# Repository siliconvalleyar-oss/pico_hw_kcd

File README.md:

# XiaoZhi - Asistente de Voz con  Raspberry pico (Versión Multisensor)

Repositorio del diseño PCB para el dispositivo **XiaoZhi**, una estación de desarrollo y asistente de voz de código abierto basado en el ****. Este diseño integra audio digital de alta calidad, iluminación RGB, pantalla OLED, **pantalla TFT**, **sensores ambientales (gas, temperatura/humedad, distancia)** y **comunicación CAN** en una sola placa diseñada con **KiCad**.

---

## 📖 Descripción

XiaoZhi evoluciona para convertirse en un nodo IoT multisensor ideal para automatización del hogar, monitoreo industrial o robótica. Además de la interacción por voz (micrófono y altavoz), la placa incorpora:

- **MQ-6**: Detección de gases combustibles (LPG, butano, metano).
- **AHT21B**: Medición precisa de temperatura y humedad ambiental (I2C).
- **VL53L0X**: Sensor de distancia por tiempo de vuelo (ToF) de hasta 2 metros.
- **ST7789**: Pantalla TFT a color para gráficos avanzados (SPI).
- **MCP2515**: Controlador CAN bus (con transceptor) para comunicación vehicular o industrial.

Todo ello manteniendo la conectividad Wi-Fi 6, BLE 5.0 y la interfaz USB-UART integrada.

---

## ✨ Características Principales

- **Microcontrolador**: Raspberry pico (RISC-V dual-core, Wi-Fi 6, BLE 5.0, Zigbee/Thread).
- **Audio**:
  - Micrófono MEMS **INMP441** (I2S).
  - Amplificador **MAX98357A** (I2S) para altavoz externo.
- **Interfaz y depuración**: **FT232** integrado para USB-UART.
- **Iluminación y control**:
  - LED GPIO estándar y LED direccionable **WS2812**.
  - Pulsadores (BOOT y RESET).
- **Pantallas**:
  - **SSD1306** (OLED 128x64, I2C) para información rápida.
  - **ST7789** (TFT a color, SPI) para gráficos, menús o visualización de datos.
- **Sensores**:
  - **MQ-6** (gas) – Salida analógica (ADC).
  - **AHT21B** (temperatura/humedad) – I2C.
  - **VL53L0X** (distancia ToF) – I2C.
- **Comunicación industrial**:
  - **MCP2515** + transceptor CAN (SPI) para bus CAN 2.0.
- **Alimentación**: 5V vía USB-C, con reguladores internos para 3.3V.

---

## 📦 Lista de Componentes (BOM)

| Componente | Cantidad | Descripción | Referencia en PCB |
| :--- | :--- | :--- | :--- |
| Raspberry pico| 1 | Módulo Wi-Fi/BLE/Zigbee | U1 |
| INMP441 | 1 | Micrófono MEMS I2S | U2 |
| MAX98357A | 1 | Amplificador Clase D I2S | U3 |
| FT232RL (o FT232RQ) | 1 | Conversor USB-UART | U4 |
| WS2812B | 1 (o N) | LED RGB direccionable | D1 |
| LED (GPIO) | 1 | LED indicador estándar | D2 |
| SWITCH (Push Button) | 2 | Pulsadores (BOOT y RESET) | SW1, SW2 |
| SSD1306 (I2C) | 1 | Display OLED de 0.96" | OLED1 |
| **MQ-6** | **1** | **Sensor de gas (LPG, butano, metano)** | **U6** |
| **AHT21B** | **1** | **Sensor de temperatura y humedad (I2C)** | **U7** |
| **VL53L0X** | **1** | **Sensor de distancia ToF (Time-of-Flight)** | **U8** |
| **ST7789** | **1** | **Pantalla TFT a color (SPI) - 1.3" / 1.54"** | **U9** |
| **PN532**|**1**|NFC |
| **MCP2515** | **1** | **Controlador CAN (SPI) + TJA1050 (transceptor)** | **U10** |
| Regulador 3.3V (AMS1117) | 1 | LDO para alimentación interna | U5 |
| Cristal 6MHz | 1 | Oscilador para FT232 (según esquema) | X1 |
| Resistencias, Capacitores, Conectores | Varios | Pasivos y terminales (USB-C, JST) | - |

---

## 🔌 Asignación de Pines (Pinout)

> **⚠️ Importante**: La siguiente tabla es una referencia estándar. Verifica siempre el esquemático (`*.sch`) para confirmar las conexiones finales.

| Periférico | Pin del ESP32-C6 | Descripción / Notas |
| :--- | :--- | :--- |
| **INMP441 (Mic)** | GPIO3 (I2S_BCK) | Bit Clock |
| | GPIO2 (I2S_WS) | Word Select (LRCLK) |
| | GPIO1 (I2S_DIN) | Data Output (DOUT) |
| | 3.3V / GND | Alimentación |
| **MAX98357A (Amp)** | GPIO3 (I2S_BCK) | Bit Clock (compartido) |
| | GPIO2 (I2S_WS) | Word Select (compartido) |
| | GPIO4 (I2S_DOUT) | Data Input (DIN) |
| | GPIO5 | Shutdown (SD) - Activo bajo |
| | 5V / GND | Alimentación |
| **WS2812** | GPIO6 | Data Input |
| | 5V / GND | Alimentación |
| **SSD1306 (OLED) / AHT21B / VL53L0X** | GPIO7 (I2C_SCL) | Bus I2C compartido (SCL) |
| | GPIO8 (I2C_SDA) | Bus I2C compartido (SDA) |
| | 3.3V / GND | Alimentación (todas comparten bus) |
| **FT232 (UART)** | GPIO9 (RX) | RX del ESP (conectar a TX del FT) |
| | GPIO10 (TX) | TX del ESP (conectar a RX del FT) |
| | GPIO11 (DTR) | Auto-reset (opcional) |
| **SWITCH BOOT** | GPIO12 | Boot (GPIO0 en otros chips, verificar) |
| **SWITCH RESET** | CHIP_EN | Reset (EN) |
| **LED GPIO** | GPIO13 | Ánodo del LED (con resistencia) |
| **MQ-6 (Gas)** | **GPIO14** | **Salida analógica (ADC)** |
| **ST7789 (TFT)** | **GPIO15 (SPI_MOSI)** | **Master Out / Slave In** |
| | **GPIO16 (SPI_SCLK)** | **Clock SPI** |
| | **GPIO17 (DC)** | **Data/Command** |
| | **GPIO18 (CS)** | **Chip Select (activo bajo)** |
| | **GPIO19 (RST)** | **Reset de la pantalla** |
| **MCP2515 (CAN)** | **GPIO15 (SPI_MOSI)** | **Comparte MOSI con TFT** |
| | **GPIO16 (SPI_SCLK)** | **Comparte SCLK con TFT** |
| | **GPIO20 (CS)** | **Chip Select exclusivo para CAN** |
| | **GPIO21 (INT)** | **Interrupción del MCP2515** |
| | 5V / GND | Alimentación (transceptor CAN) |

---

## 🧩 Integración de Sensores y Bus Compartido

Para optimizar los pines del Raspberry pico , el diseño utiliza buses compartidos:

- **Bus I2C (GPIO7 y GPIO8)**: Conecta simultáneamente el **SSD1306**, el **AHT21B** y el **VL53L0X**. Cada dispositivo tiene una dirección I2C única, por lo que no hay conflicto.
- **Bus SPI (GPIO15 y GPIO16)**: Conecta el **ST7789** y el **MCP2515**. Se diferencian mediante pines **CS (Chip Select)** independientes (GPIO18 para TFT, GPIO20 para CAN).
- **ADC (GPIO14)**: Reservado exclusivamente para la salida analógica del sensor de gas **MQ-6**. Se recomienda agregar un capacitor de filtrado en la PCB para estabilizar la lectura.

---

## 🛠️ Uso del Proyecto en KiCad

### Requisitos
- KiCad **v8.0** o superior.
- Símbolos y huellas adicionales para los nuevos componentes (es posible que necesites descargar librerías externas para el MCP2515, VL53L0X o ST7789).

### Abrir y Editar
1. Clona este repositorio:
   ```bash
   git clone https://github.com/tu-usuario/xiaozhi-pcb.git
   cd xiaozhi-pcb

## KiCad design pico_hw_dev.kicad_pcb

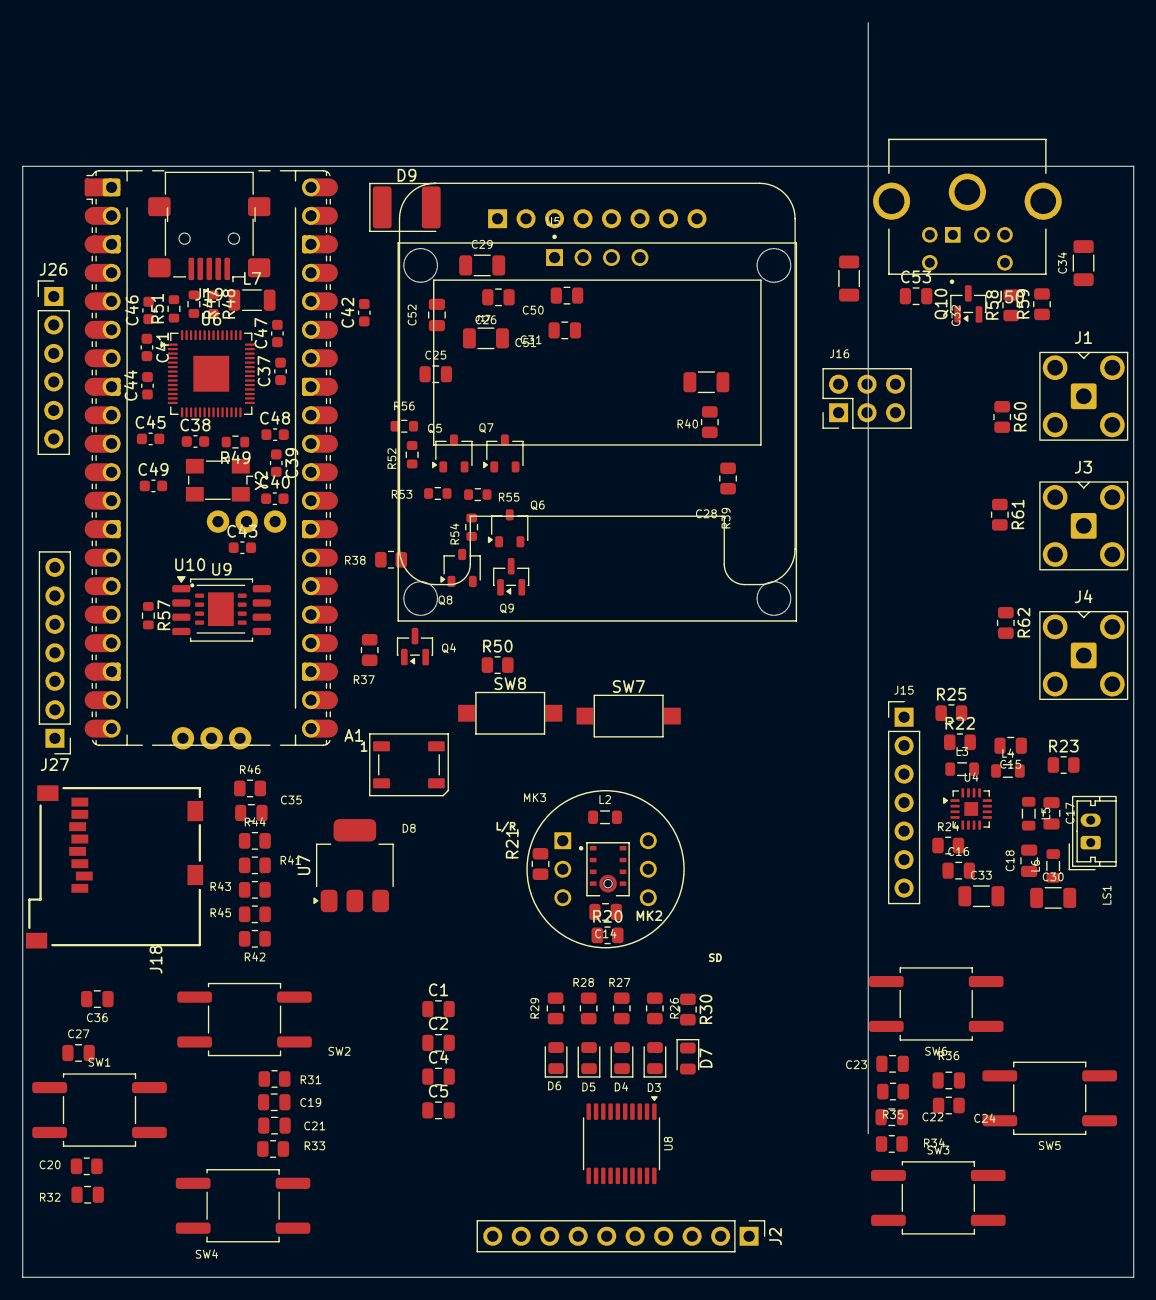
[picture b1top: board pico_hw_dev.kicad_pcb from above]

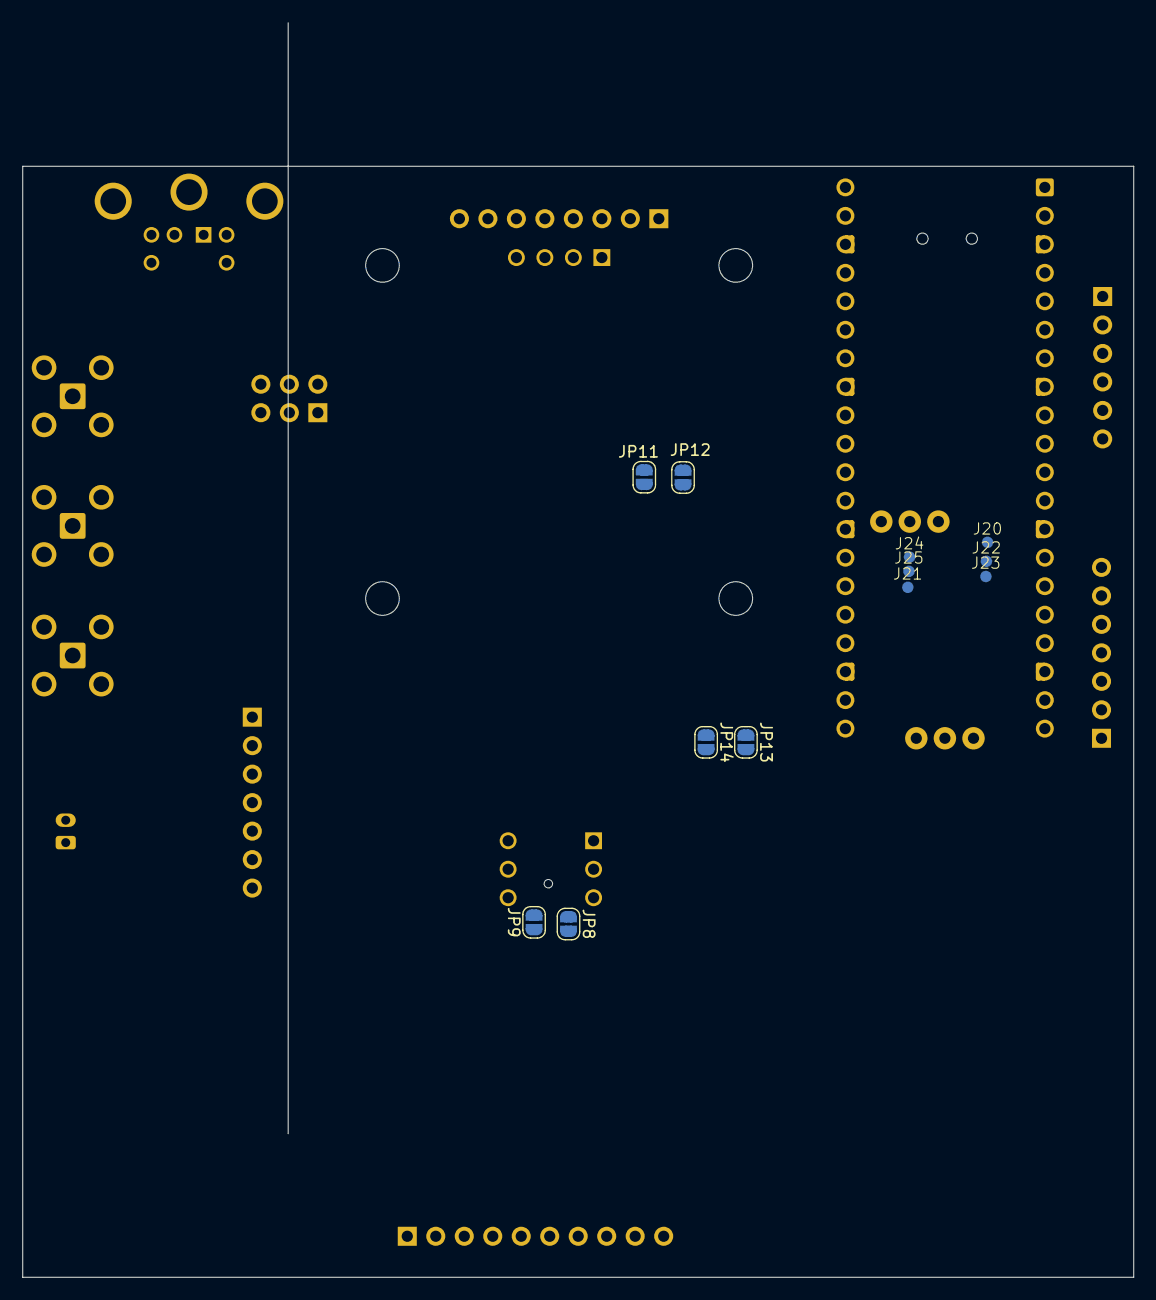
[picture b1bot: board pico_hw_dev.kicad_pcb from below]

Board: 2 copper layers, 99.1 x 99.1 mm, 151 parts (12 on the bottom side), 90 nets, no tracks yet.

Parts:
A1: RaspberryPi_Pico
C1, C2, C4, C5, C14, C15, C19, C20, C21, C22, C23, C24, C26, C27, C35, C36, C50, C51, C52: 100nf; C_0805_2012Metric
C16: 10uf; C_0805_2012Metric
C17: 220p; C_0805_2012Metric
C18: 22p; C_0805_2012Metric
C25: 100nF; C_0805_2012Metric
C28, C29, C30, C31, C32, C33, C34: 100nf; C_1206_3216Metric
C37, C38, C39, C40, C41, C42, C43, C44, C45, C46, C48: 10n; C_0603_1608Metric
C47, C49: 100nf; C_0603_1608Metric
C53: 10n; C_0805_2012Metric
D3, D4, D5, D6, D7: LED; D_0805_2012Metric
D8: WS2812B; LED_WS2812B_PLCC4_5.0x5.0mm_P3.2mm
D9: D_Schottky; D_2114_3652Metric
J1, J3, J4: Conn_Coaxial; SMA_BAT_Wireless_BWSMA-KWE-Z001
J2: LOGIC; PinHeader_1x10_P2.54mm_Vertical
J15: PinHeader_1x07_P2.54mm_Vertical
J16: Oled SSD1306 128x32; PinHeader_2x03_P2.54mm_Vertical
J17: Adafruit ST7789; Adafruit_SSD1306_No_Mounting_Holes_pads
J18: Micro_SD_Card; 3M_2908-05WB-MG
J19: USB_B_Mini; USB_Mini-B_Lumberg_2486_01_Horizontal
J20, J21, J22, J23, J24, J25: gpio_rp2040; connector_pin_smd_1mm
J26: FT232RL; PinHeader_1x06_P2.54mm_Vertical
J27: picoprobe debugger; PinHeader_1x07_P2.54mm_Vertical
J50: Mini-DIN-6; TE_5749180-1
JP8, JP9: Jumper_2_Open; SolderJumper-2_P1.3mm_Open_RoundedPad1.0x1.5mm
JP11, JP12, JP13, JP14: NL; SolderJumper-2_P1.3mm_Open_RoundedPad1.0x1.5mm
L2, L3, L4, L5, L6: ferrite; L_0805_2012Metric
L7: 100mh; L_1206_3216Metric
LS1: Speaker; Molex_Micro-Latch_53253-0270_1x02_P2.00mm_Vertical
MK2: INMP441ACEZ-R7; MIC_INMP441ACEZ-R7
MK3: INMP441ACEZ-R7; MODULE_OKY3139
Q4, Q9, Q10: 2N7002; SOT-23
Q5, Q7: Q_NPN_BCE; SOT-23W
Q6, Q8: FDN306P; SOT-23W
R20, R21, R22, R23: 100k; R_0805_2012Metric
R24: 1M; R_0805_2012Metric
R25: 68k; R_0805_2012Metric
R26, R27, R28, R29, R30, R31, R32, R33, R34, R35, R36, R37, R38, R39, R40: 2k2; R_0805_2012Metric
R41, R42, R43, R44, R45, R46: 4k7; R_0805_2012Metric
R47, R48, R49, R51, R52, R53, R54, R55, R56, R57: 10k; R_0603_1608Metric
R50, R58, R59, R60, R61, R62: 10k; R_0805_2012Metric
SW1, SW5: up; SW_Push_1P1T_NO_CK_KSC9xxG
SW2, SW6: down; SW_Push_1P1T_NO_CK_KSC9xxG
SW3: left; SW_Push_1P1T_NO_CK_KSC9xxG
SW4: rigth; SW_Push_1P1T_NO_CK_KSC9xxG
SW7: boot; SW_SPST_CK_RS282G05A3
SW8: run; SW_SPST_CK_RS282G05A3
U4: MAX98357A; TQFN-16-1EP_3x3mm_P0.5mm_EP1.23x1.23mm
U5: ER_OLEDM0.91_1x-I2C; LCD_OLED_128X64_1.3_I2C
U6: RP2040; QFN-56-1EP_7x7mm_P0.4mm_EP3.2x3.2mm
U7: R-78E3.3-0.5; SOT-223-3_TabPin2
U8: TXS0108EPW; TSSOP-20_4.4x6.5mm_P0.65mm
U9: W25Q16JVSS; SOIC-8_5.3x5.3mm_P1.27mm
U10: W25Q16JVSS; Winbond_XSON-8-1EP_4x4mm_P0.8mm_EP2.3x3.0mm
Y2: Crystal_GND24_Small; Oscillator_SMD_Fox_FT5H_5.0x3.2mm

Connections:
+1V2: C40.2, C41.2, U6.23 (DVDD), U6.45 (VREG_VOUT), U6.50 (DVDD)
+3.3V: A1.36 (3V3), A1.37 (3V3_EN), C1.1, C2.1, C4.2, C5.2, C42.2, C43.2, C44.2, C45.2, C49.2, Q10.1 (G), R50.1, R51.2, R58.2, U6.1 (IOVDD), U6.10 (IOVDD), U6.22 (IOVDD), U6.33 (IOVDD), U6.42 (IOVDD), U6.43 (ADC_AVDD), U6.44 (VREG_IN), U6.48 (USB_VDD), U6.49 (IOVDD), U7.3 (OUT), U9.8 (VCC), U10.8 (VCC)
+3V3: C26.1, C27.1, C28.1, C29.1, C30.1, C31.1, C32.1, C35.1, C36.1, C50.1, C51.1, J16.1, J17.2, J18.4 (VDD), JP8.2 (B), JP11.2 (B), L2.2, L3.2, Q4.1 (G), R24.1, R31.1, R32.1, R33.1, R34.1, R35.1, R36.1, R37.2, R39.1, R40.1, R41.1, R42.1, R43.1, R44.2, R45.1, R46.2, R53.2, R56.2, U5.2 (VCC), U8.2 (VCCA)
+5V: C25.1, C33.1, C34.1, C52.1, C53.1, D8.1 (VDD), J16.2, J16.4, J50.4, JP12.2 (B), L4.2, R38.2, R59.2, U8.19 (VCCB)
/ADC_0: A1.31 (GPIO26_ADC0), J50.1, Q10.2 (S), Q10.3 (D), R58.1, R59.1, U6.38 (GPIO26_ADC0)
/ADC_1: A1.32 (GPIO27_ADC1), J50.5, U6.39 (GPIO27_ADC1)
/ADC_2: A1.34 (GPIO28_ADC2), U6.40 (GPIO28_ADC2)
/IO_4: A1.6 (GPIO4), J15.1, U4.14 (LRCLK), U6.6 (GPIO4)
/IO_5: A1.7 (GPIO5), D5.2 (A), U6.7 (GPIO5), U8.4 (A3)
/IO_6: A1.9 (GPIO6), D6.2 (A), U6.8 (GPIO6), U8.5 (A4)
/IO_7: A1.10 (GPIO7), C20.1, R32.2, SW1.1, U6.9 (GPIO7), U8.6 (A5)
/IO_8: A1.11 (GPIO8), C19.1, R31.2, SW2.1, U6.11 (GPIO8), U8.7 (A6)
/IO_9: A1.12 (GPIO9), C22.1, R34.2, SW3.1, U6.12 (GPIO9), U8.8 (A7)
/IO_10: A1.14 (GPIO10), MK2.1 (SCK), MK3.1 (SCK), U6.13 (GPIO10)
/IO_11: A1.15 (GPIO11), MK2.3 (WS), MK3.3 (WS), U6.14 (GPIO11)
/IO_13: A1.17 (GPIO13), C21.1, R33.2, SW4.1, U6.16 (GPIO13), U8.9 (A8)
/IO_23: C24.1, R36.2, SW5.1, U6.35 (GPIO23)
/IO_24: C23.1, R35.2, SW6.1, U6.36 (GPIO24)
/IO_25: JP13.1 (A), U6.37 (GPIO25)
/Logic_convert/B1: J2.2, U8.20 (B1)
/Logic_convert/B2: J2.3, U8.18 (B2)
/Logic_convert/B3: J2.4, U8.17 (B3)
/Logic_convert/B4: J2.5, U8.16 (B4)
/Logic_convert/B5: J2.6, U8.15 (B5)
/Logic_convert/B6: J2.7, U8.14 (B6)
/Logic_convert/B7: J2.8, U8.13 (B7)
/Logic_convert/B8: J2.9, U8.12 (B8)
/Logic_convert/OEN: Q7.2 (C), R56.1, U8.10 (OE)
/Logic_convert/vcc: J2.1, Q8.2
/MISO: A1.21 (GPIO16), J18.3 (CMD), R42.2, U6.27 (GPIO16)
/WS2812: JP13.2 (B), JP14.2 (B), Q4.2 (S), Q6.1, Q9.1 (G), R37.1, R54.2
/inmp441/EN: C14.2, L2.1, MK2.7 (VDD), MK2.8 (CHIPEN)
/max98357a/OUTN: L5.1, U4.10 (OUTN)
/max98357a/OUTP: L6.1, U4.9 (OUTP)
/picohw/QSPI_CS: J20.1 (Pin_1_1), R51.1, R57.1, U6.56 (QSPI_SS), U9.1 (~CS), U10.1 (~CS)
/picohw/QSPI_SCLK: J25.1 (Pin_1_1), U6.52 (QSPI_SCLK), U9.6 (CLK), U10.6 (CLK)
/picohw/QSPI_SD0: J21.1 (Pin_1_1), U6.53 (QSPI_SD0), U9.5 (DI/IO_{0}), U10.5 (DI/IO_{0})
/picohw/QSPI_SD1: J22.1 (Pin_1_1), U6.55 (QSPI_SD1), U9.2 (DO/IO_{1}), U10.2 (DO/IO_{1})
/picohw/QSPI_SD2: J23.1 (Pin_1_1), U6.54 (QSPI_SD2), U9.3 (~WP/IO_{2}), U10.3 (~WP/IO_{2})
/picohw/QSPI_SD3: J24.1 (Pin_1_1), U6.51 (QSPI_SD3), U9.7 (~HOLD/~RESET/IO_{3}), U10.7 (~HOLD/~RESET/IO_{3})
/picohw/RUN: A1.30 (RUN), C48.1, R50.2, SW8.2, U6.26 (RUN)
/picohw/USB_DM: R47.2, U6.46 (USB_DM)
/picohw/USB_DP: R48.2, U6.47 (USB_DP)
/picohw/XIN: C38.1, U6.20 (XIN), Y2.3
/picohw/XOUT: R49.2, U6.21 (XOUT)
/swclk: J27.5, U6.24 (SWCLK)
/swdio: J27.4, U6.25 (SWD)
BLK_ST7789: A1.29 (GPIO22), J17.7, U6.34 (GPIO22)
CLK_ST7789: A1.19 (GPIO14), J17.4, U6.17 (GPIO14)
CS_RP2040: A1.22 (GPIO17), J18.2 (DAT3/CD), R43.2, U6.28 (GPIO17)
DC_ST7789: A1.27 (GPIO21), J16.5, J17.6, R39.2, U5.3 (SCL), U6.32 (GPIO21)
DI_ST7789: A1.20 (GPIO15), J17.3, U6.18 (GPIO15)
GAIN: J15.4, R22.2, R23.1, U4.2 (GAIN_SLOT)
GND: A1.3 (GND), A1.8 (GND), A1.13 (GND), A1.18 (GND), A1.23 (GND), A1.28 (GND), A1.33 (AGND), A1.38 (GND), C1.2, C2.2, C4.1, C5.1, C14.1, C15.1, C16.1, C17.1, C18.1, C19.2, C20.2, C21.2, C22.2, C23.2, C24.2, C25.2, C26.2, C27.2, C28.2, C29.2, C30.2, C31.2, C32.2, C33.2, C34.2, C35.2, C36.2, C37.1, C38.2, C39.2, C40.1, C41.1, C42.1, C43.1, C44.1, C45.1, C46.2, C47.1, C48.2, C49.1, C50.2, C51.2, C52.2, C53.2, D8.3 (VSS), J1.2 (Ext), J2.10, J3.2 (Ext), J4.2 (Ext), J15.6, J16.6, J17.1, J18.6 (VSS), J19.5 (GND), J26.6, J27.3, J50.3, JP8.1 (A), JP9.1 (A), JP9.2 (B), MK2.4 (L/R), MK2.5 (GND), MK2.6 (GND), MK2.9 (GND), MK3.4 (L/R), MK3.5 (GND), MK3.6 (GND), Q5.3 (E), Q7.3 (E), Q9.2 (S), R20.1, R20.2, R21.2, R23.2, R26.1, R27.1, R28.1, R29.1, R30.1, R54.1, SW1.2, SW2.2, SW3.2, SW4.2, SW5.2, SW6.2, SW7.1, SW8.1, U4.3 (GND), U4.11 (GND), U4.15 (GND), U4.17 (PAD), U5.1 (GND), U6.19 (TESTEN), U6.57 (GND), U7.2 (GND), U8.11 (GND), U9.4 (GND), U10.4 (GND), Y2.2, Y2.4
LED_Data_5V: D8.4 (DIN), Q4.3 (D), R38.1
MIDE_FRECUENCY: A1.35 (ADC_VREF), JP14.1 (A), U6.41 (GPIO29_ADC3)
MOSI_RP_2040: A1.25 (GPIO19), J18.7 (DAT0), R44.1, U6.30 (GPIO19)
MSCLK_RP_2040: A1.24 (GPIO18), J18.1 (DAT2), R45.2, U6.29 (GPIO18)
unnamed: C17.2, L5.2, LS1.2
unnamed: C18.2, L6.2, LS1.1
unnamed: C39.1, R49.1, Y2.1
unnamed: D3.1 (K), R26.2
unnamed: D4.1 (K), R27.2
unnamed: D5.1 (K), R28.2
unnamed: D6.1 (K), R29.2
unnamed: D7.1 (K), R30.2
unnamed: C37.2, D9.2 (A), J19.1 (VBUS)
unnamed: J1.1 (In), R60.1
unnamed: J3.1 (In), R61.1
unnamed: J4.1 (In), R62.1
unnamed: J18.5 (CLK), R41.2
unnamed: J18.8 (DAT1), R46.1
unnamed: J19.3 (D+), R48.1
unnamed: J19.2 (D-), R47.1
unnamed: JP11.1 (A), JP12.1 (A), Q6.3, Q8.3
unnamed: Q5.1 (B), R52.2
unnamed: Q5.2 (C), R53.1, R55.1
unnamed: Q7.1 (B), R55.2
unnamed: Q6.2, Q8.1, Q9.3 (D)
unnamed: R57.2, SW7.2
unnamed: R25.2, U4.4 (~SD_MODE)
unnamed: C47.2, L7.2, U7.1 (IN)
RES_ST7789: A1.26 (GPIO20), J16.3, J17.5, R40.2, U5.4 (SDA), U6.31 (GPIO20)
RX_RP2040: A1.2 (GPIO1), D4.2 (A), U6.3 (GPIO1), U8.3 (A2)
SCL_RPI: A1.5 (GPIO3), J15.2, U4.16 (BCLK), U6.5 (GPIO3)
SD: A1.16 (GPIO12), J15.5, MK2.2 (SD), MK3.2 (SD), R21.1, R24.2, R25.1, U6.15 (GPIO12)
SDA_RPI: A1.4 (GPIO2), J15.3, U4.1 (DIN), U6.4 (GPIO2)
TX_RP2040: A1.1 (GPIO0), D3.2 (A), U6.2 (GPIO0), U8.1 (A1)
V+_USB_MCU_RP2040: A1.40 (VBUS), C46.1, D9.1 (K), L7.1
VCC_MAX98357: C15.2, C16.2, J15.7, L3.1, L4.1, R22.1, U4.7 (VDD), U4.8 (VDD)

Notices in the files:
README.md:
License: MIT
